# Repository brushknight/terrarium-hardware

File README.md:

## I have to pull this project back from public because I am considering manufacturing of the controller and for a period of time we will not publish schematics. Once I release controller I will consider publishing schematics again.

---

# Terrarium controller (esp32 based)
[more details here](./controller/README.md)

This terrarium controller is capable of controlling set temperature, heat, and UVB lamps taking into account the time of the day.

## Features
- ESP32 WROOM 32 as a main brain of the system
- EEPROM i2c DIP-8 socket for user configuration storage
- 6 x 5v i2c & 1wire sensors
- 4 x 5v SSR to drive up to 3 x 220v2A loads
  - Protected by SMD fuse with max current limited to 1.5A/220V
- 2 x 5v 3/4pin PWM fan support
- i2c Display to show crusial information
- i2c RTC DS3231M + battery to keep time between power outages
- i2c multiplexer TCA9548APWR
- i2c IO expander PCF8574
- i2c extensions port
- cp2102 USB to UART
  - It is bidirectional now
  - Includes ESD protection
- USB-C for power and flashing
- 0805 components size

---

# Terrarium dimmer (esp32 based)
[more details here](./dimmer/README.md)

This terrarium dimmer is capable of controlling brightness of the incandescent lamps taking into account the time of the day.

## Features
- ESP32 WROOM 32 as a main brain of the system
- 2 pwm dimmer modules
- i2c extension port (used for connecting to the main controller)
- cp2102 USB to UART
- USB-C for power and flashing

---

# Terrarium light dome (esp32 based)
[more details here](./light_dome/README.md)

This terrarium dome is capable to provide some light with simple ws2812b LEDs. The meain goal right now is to create circadian lights for the reptiles so it is not on/off of the UVB bulb.

In the next iterations I am planning to do a research about UV LEDs and other more reptiles oriented LEDs.

## Features
- ESP32 WROOM 32 as a main brain of the system
- 20 x 3 (60 in total) ws2812b LEDs
- i2c extension port (used for connecting to the main controller)
- cp2102 USB to UART
- USB-C for power and flashing

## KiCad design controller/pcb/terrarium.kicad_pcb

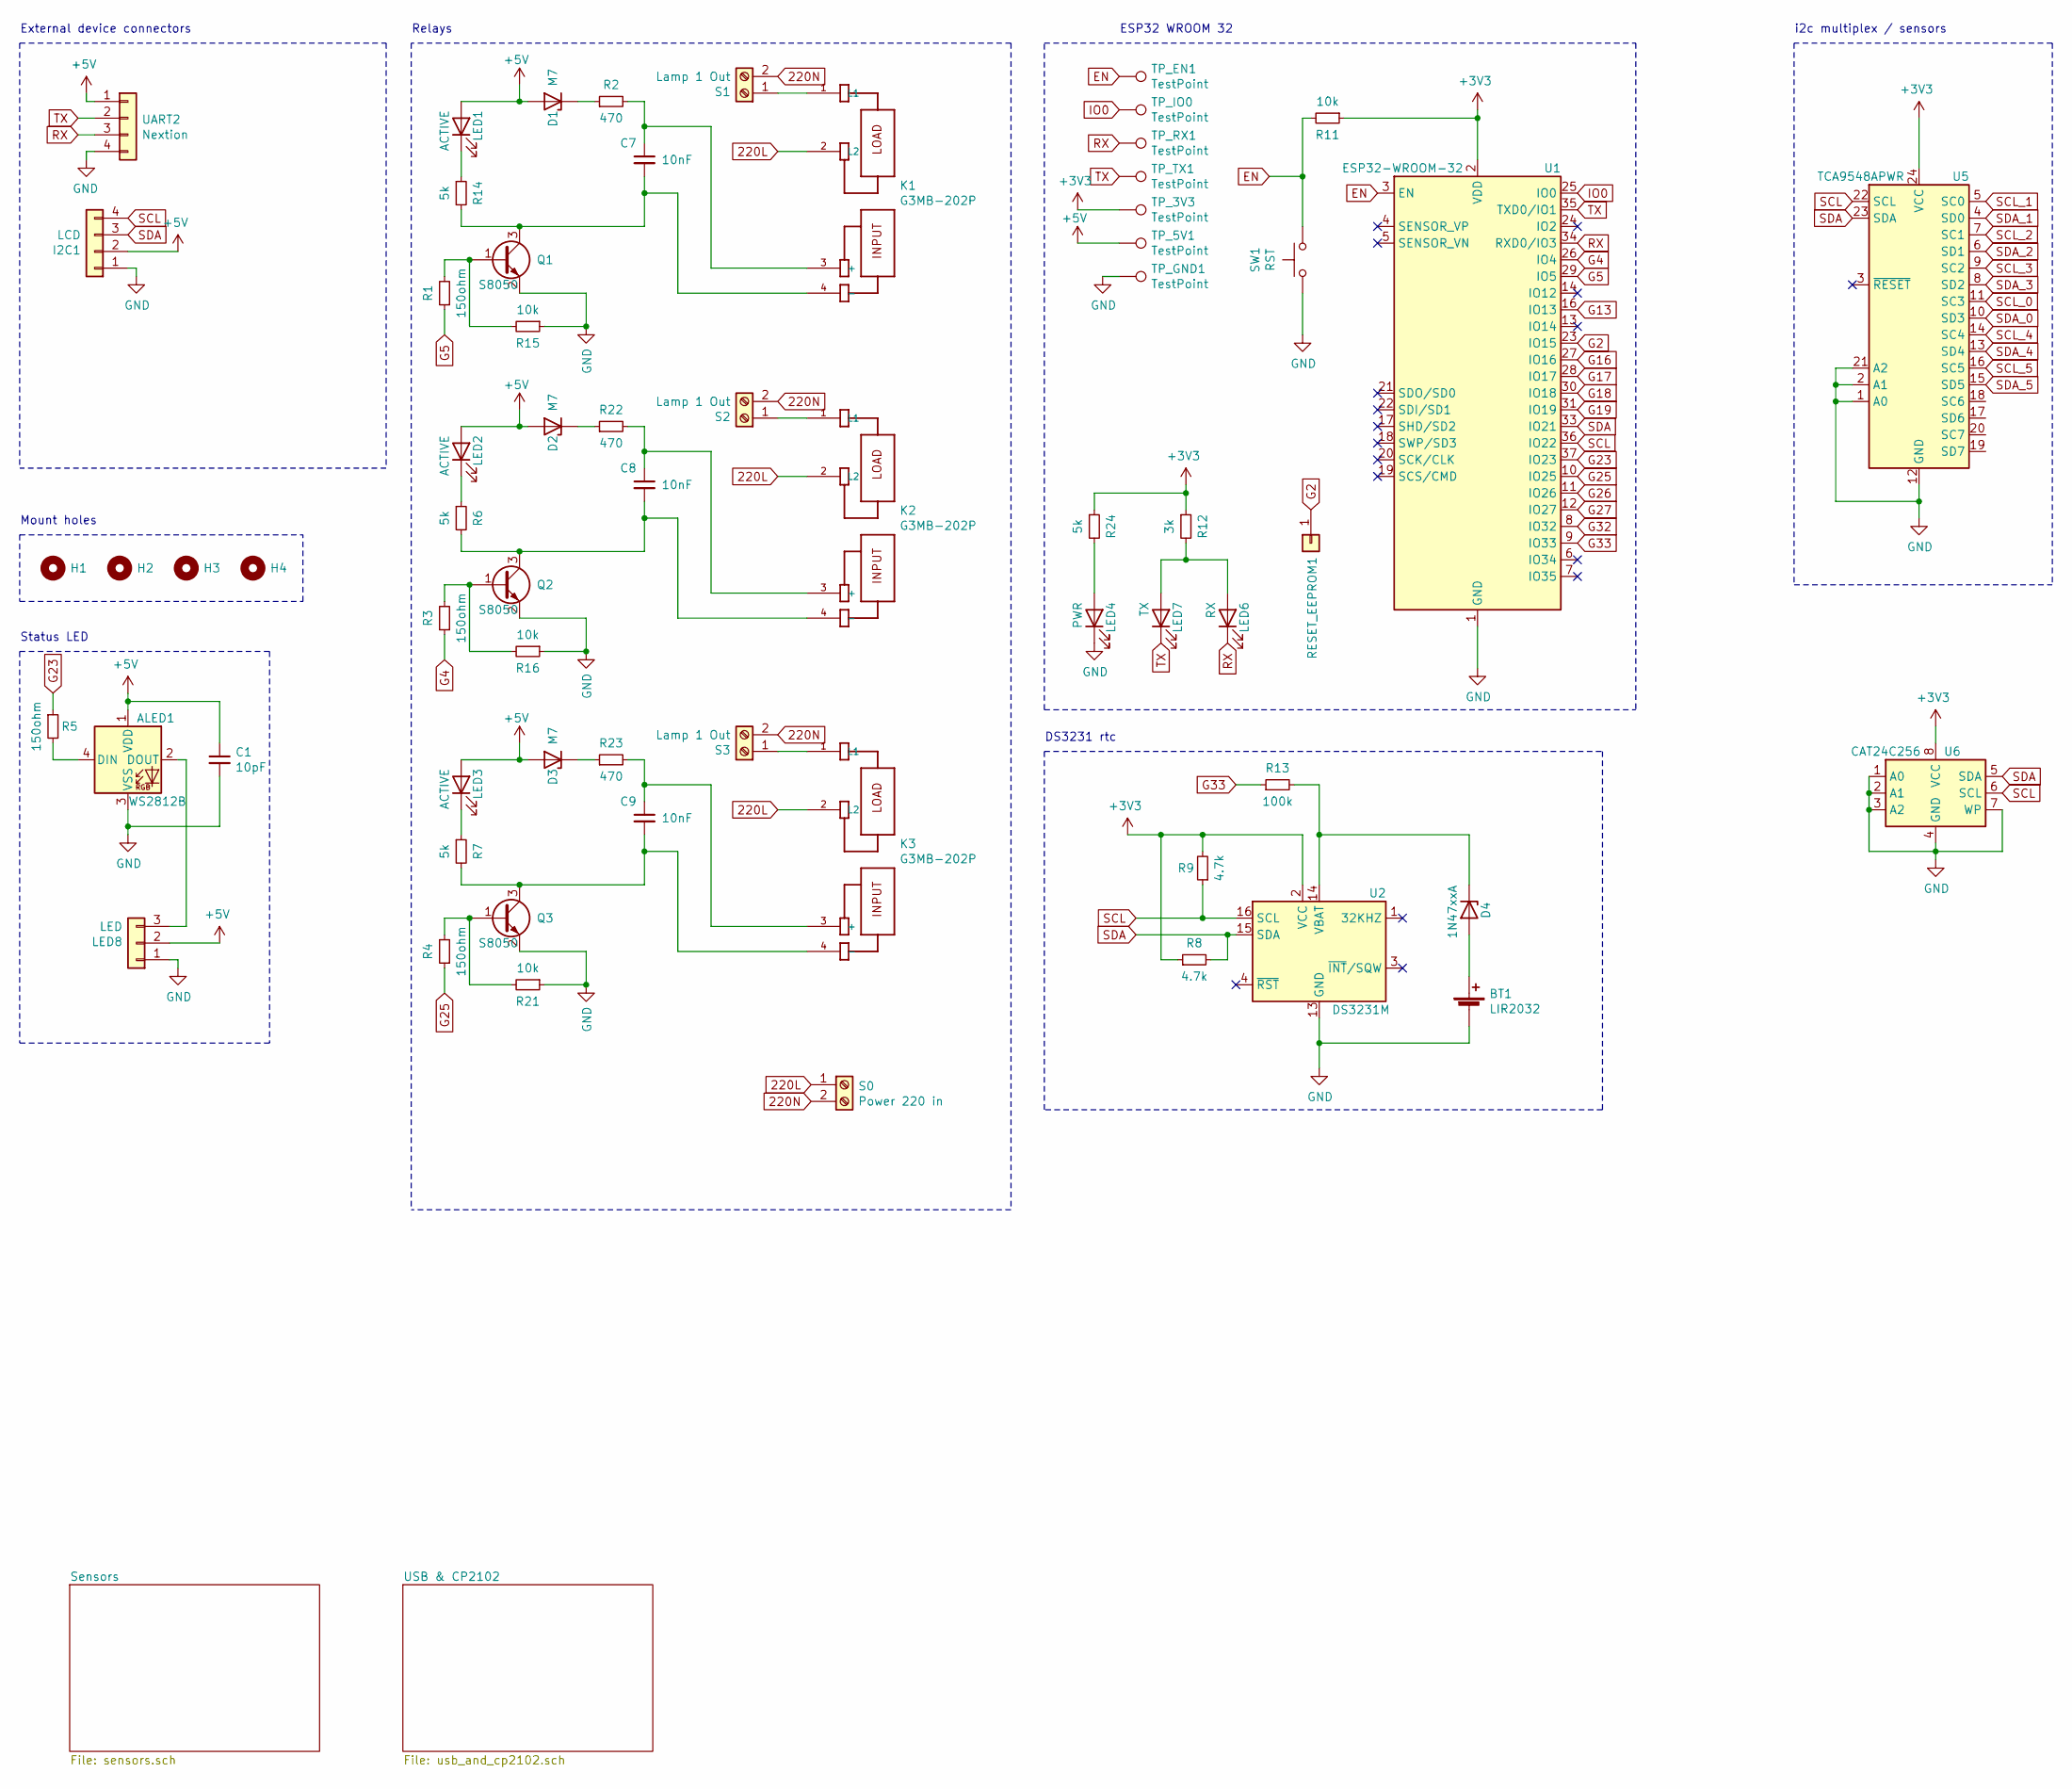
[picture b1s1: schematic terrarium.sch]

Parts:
ALED1: WS2812B; LED_WS2812B_PLCC4_5.0x5.0mm_P3.2mm
BT1: LIR2032; CR2032_vertical
C1: 10pF; C_1206_3216Metric
C7, C8, C9: 10nF; C_1206_3216Metric
D1, D2, D3: M7; D_2010_5025Metric
D4: 1N47xxA; D_2010_5025Metric
H1, H2, H3, H4: MountingHole; MountingHole_3.2mm_M3_Pad_Via
I2C1: LCD; JST_XH_B4B-XH-AM_1x04_P2.50mm_Vertical
K1, K2, K3: G3MB-202P; RELAY_G3MB-202P
LED1, LED2, LED3: ACTIVE; LED_1206_3216Metric
LED4: PWR; LED_1206_3216Metric
LED6: RX; LED_1206_3216Metric
LED7: TX; LED_1206_3216Metric
LED8: LED; JST_XH_B3B-XH-A_1x03_P2.50mm_Vertical
Q1, Q2, Q3: S8050; SOT-23
R1, R3, R4, R5: 150ohm; R_1206_3216Metric
R2, R22, R23: 470; R_1206_3216Metric
R6, R7, R14, R24: 5k; R_1206_3216Metric
R8, R9: 4.7k; R_1206_3216Metric
R11, R15, R16, R21: 10k; R_1206_3216Metric
R12: 3k; R_1206_3216Metric
R13: 100k; R_1206_3216Metric
RESET_EEPROM1: data; PinHeader_1x01_P2.54mm_Vertical
S0: Power 220 in; TerminalBlock_bornier-2_P5.08mm
S1, S2, S3: Lamp 1 Out; TerminalBlock_bornier-2_P5.08mm
SW1: RST; SW_Tactile_SPST_Angled_PTS645Vx39-2LFS
TP_3V3, TP_5V1: TestPoint; TestPoint_Pad_1.5x1.5mm
TP_EN1: TestPoint; TestPoint_Pad_1.5x1.5mm
TP_GND1: TestPoint; TestPoint_Pad_1.5x1.5mm
TP_IO0: TestPoint; TestPoint_Pad_1.5x1.5mm
TP_RX1: TestPoint; TestPoint_Pad_1.5x1.5mm
TP_TX1: TestPoint; TestPoint_Pad_1.5x1.5mm
U1: ESP32-WROOM-32
U2: DS3231M; SOIC-16W_7.5x10.3mm_P1.27mm
U5: TCA9548APWR; TSSOP-24_4.4x7.8mm_P0.65mm
U6: CAT24C256; DIP-8_W7.62mm_Socket
UART2: Nextion; JST_XH_B4B-XH-AM_1x04_P2.50mm_Vertical

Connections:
220L: K1.2 (L2), K2.2 (L2), K3.2 (L2), S0.1
220N: S0.2, S1.2, S2.2, S3.2
+3V3: R8.1, R9.2, R11.1, R12.1, R24.1, TP_3V3.1, U1.2 (VDD), U2.2 (VCC), U5.24 (VCC), U6.8 (VCC); also elsewhere on the board
+5V: ALED1.1 (VDD), C1.1, D1.2 (A), D2.2 (A), D3.2 (A), I2C1.2, LED1.2 (A), LED2.2 (A), LED3.2 (A), LED8.2, TP_5V1.1, UART2.1; also elsewhere on the board
EN: R11.2, SW1.2, TP_EN1.1, U1.3 (EN); also elsewhere on the board
G2: RESET_EEPROM1.1, U1.23 (IO15)
G4: R3.1, U1.26 (IO4)
G5: R1.1, U1.29 (IO5)
G13: U1.16 (IO13)
G16: U1.27 (IO16); also elsewhere on the board
G17: U1.28 (IO17); also elsewhere on the board
G18: U1.30 (IO18); also elsewhere on the board
G19: U1.31 (IO19); also elsewhere on the board
G23: R5.1, U1.37 (IO23)
G25: R4.1, U1.10 (IO25)
G26: U1.11 (IO26); also elsewhere on the board
G27: U1.12 (IO27); also elsewhere on the board
G32: U1.8 (IO32); also elsewhere on the board
G33: R13.1, U1.9 (IO33)
GND: ALED1.3 (VSS), BT1.2 (-), C1.2, I2C1.1, LED4.1 (K), LED8.1, Q1.2 (E), Q2.2 (E), Q3.2 (E), R15.1, R16.1, R21.1, SW1.1, TP_GND1.1, U1.1 (GND), U1.15 (GND), U1.38 (GND), U1.39 (GND), U2.5 (GND), U2.6 (GND), U2.7 (GND), U2.8 (GND), U2.9 (GND), U2.10 (GND), U2.11 (GND), U2.12 (GND), U2.13 (GND), U5.1 (A0), U5.2 (A1), U5.12 (GND), U5.21 (A2), U6.1 (A0), U6.2 (A1), U6.3 (A2), U6.4 (GND), U6.7 (WP), UART2.4; also elsewhere on the board
IO0: TP_IO0.1, U1.25 (IO0); also elsewhere on the board
unnamed: ALED1.2 (DOUT), LED8.3
unnamed: ALED1.4 (DIN), R5.2
unnamed: BT1.1 (+), D4.2 (A)
unnamed: C7.1, K1.3 (+), R2.2
unnamed: C7.2, K1.4 (-), Q1.3 (C), R14.2
unnamed: C8.1, K2.3 (+), R22.2
unnamed: C8.2, K2.4 (-), Q2.3 (C), R6.2
unnamed: C9.1, K3.3 (+), R23.2
unnamed: C9.2, K3.4 (-), Q3.3 (C), R7.2
unnamed: D1.1 (K), R2.1
unnamed: D2.1 (K), R22.1
unnamed: D3.1 (K), R23.1
unnamed: D4.1 (K), R13.2, U2.14 (VBAT)
unnamed: K1.1 (L1), S1.1
unnamed: K2.1 (L1), S2.1
unnamed: K3.1 (L1), S3.1
unnamed: LED1.1 (K), R14.1
unnamed: LED2.1 (K), R6.1
unnamed: LED3.1 (K), R7.1
unnamed: LED4.2 (A), R24.2
unnamed: LED6.2 (A), LED7.2 (A), R12.2
unnamed: Q1.1 (B), R1.2, R15.2
unnamed: Q2.1 (B), R3.2, R16.2
unnamed: Q3.1 (B), R4.2, R21.2
unnamed 58: U5.3 (~RESET); also elsewhere on the board
RX: LED6.1 (K), TP_RX1.1, U1.34 (RXD0/IO3), UART2.3; also elsewhere on the board
SCL: I2C1.4, R9.1, U1.36 (IO22), U2.16 (SCL), U5.22 (SCL), U6.6 (SCL); also elsewhere on the board
SCL_0: U5.11 (SC3); also elsewhere on the board
SCL_1: U5.5 (SC0); also elsewhere on the board
SCL_2: U5.7 (SC1); also elsewhere on the board
SCL_3: U5.9 (SC2); also elsewhere on the board
SCL_4: U5.14 (SC4); also elsewhere on the board
SCL_5: U5.16 (SC5); also elsewhere on the board
SDA: I2C1.3, R8.2, U1.33 (IO21), U2.15 (SDA), U5.23 (SDA), U6.5 (SDA); also elsewhere on the board
SDA_0: U5.10 (SD3); also elsewhere on the board
SDA_1: U5.4 (SD0); also elsewhere on the board
SDA_2: U5.6 (SD1); also elsewhere on the board
SDA_3: U5.8 (SD2); also elsewhere on the board
SDA_4: U5.13 (SD4); also elsewhere on the board
SDA_5: U5.15 (SD5); also elsewhere on the board
TX: LED7.1 (K), TP_TX1.1, U1.35 (TXD0/IO1), UART2.2; also elsewhere on the board

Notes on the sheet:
External device connectors
Relays
Status LED
ESP32 WROOM 32
DS3231 rtc
Mount holes
i2c multiplex / sensors

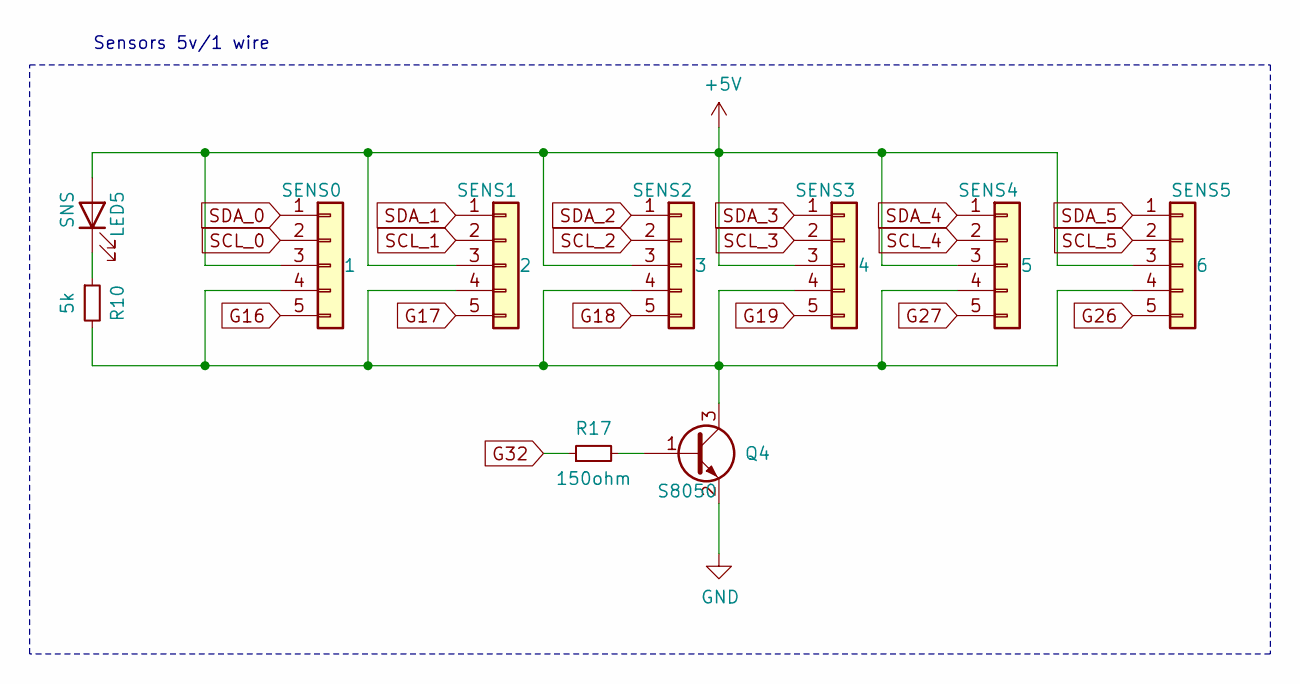
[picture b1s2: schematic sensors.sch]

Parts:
LED5: SNS; LED_1206_3216Metric
Q4: S8050; SOT-23
R10: 5k; R_1206_3216Metric
R17: 150ohm; R_1206_3216Metric
SENS0: 1; JST_XH_B5B-XH-A_1x05_P2.50mm_Vertical
SENS1: 2; JST_XH_B5B-XH-A_1x05_P2.50mm_Vertical
SENS2: 3; JST_XH_B5B-XH-A_1x05_P2.50mm_Vertical
SENS3: 4; JST_XH_B5B-XH-AM_1x05_P2.50mm_Vertical
SENS4: 5; JST_XH_B6B-XH-AM_1x06_P2.50mm_Vertical
SENS5: 6; JST_XH_B5B-XH-A_1x05_P2.50mm_Vertical

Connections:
+5V: LED5.2 (A), SENS0.3, SENS1.3, SENS2.3, SENS3.3, SENS4.3, SENS5.3; also elsewhere on the board
G16: SENS0.5; also elsewhere on the board
G17: SENS1.5; also elsewhere on the board
G18: SENS2.5; also elsewhere on the board
G19: SENS3.5; also elsewhere on the board
G26: SENS5.5; also elsewhere on the board
G27: SENS4.5; also elsewhere on the board
G32: R17.1; also elsewhere on the board
GND: Q4.2 (E); also elsewhere on the board
unnamed: LED5.1 (K), R10.1
unnamed: Q4.1 (B), R17.2
unnamed: Q4.3 (C), R10.2, SENS0.4, SENS1.4, SENS2.4, SENS3.4, SENS4.4, SENS5.4
SCL_0: SENS0.2; also elsewhere on the board
SCL_1: SENS1.2; also elsewhere on the board
SCL_2: SENS2.2; also elsewhere on the board
SCL_3: SENS3.2; also elsewhere on the board
SCL_4: SENS4.2; also elsewhere on the board
SCL_5: SENS5.2; also elsewhere on the board
SDA_0: SENS0.1; also elsewhere on the board
SDA_1: SENS1.1; also elsewhere on the board
SDA_2: SENS2.1; also elsewhere on the board
SDA_3: SENS3.1; also elsewhere on the board
SDA_4: SENS4.1; also elsewhere on the board
SDA_5: SENS5.1; also elsewhere on the board

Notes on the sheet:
Sensors 5v/1 wire

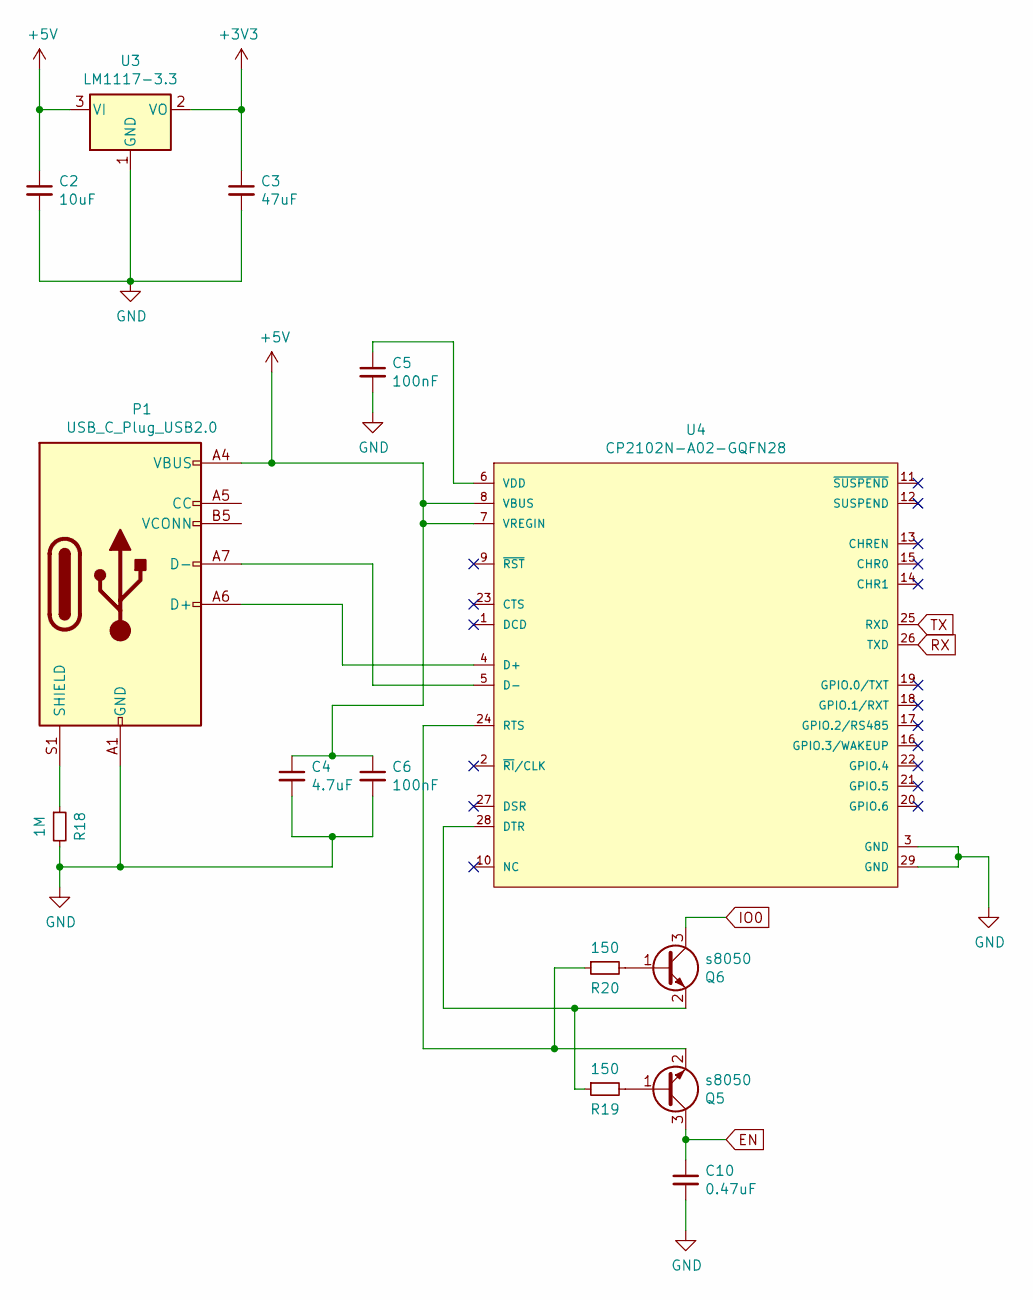
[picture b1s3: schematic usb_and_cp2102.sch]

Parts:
C2: 10uF; C_1206_3216Metric
C3: 47uF; C_1206_3216Metric
C4: 4.7uF; C_1206_3216Metric
C5, C6: 100nF; C_1206_3216Metric
C10: 0.47uF; C_1206_3216Metric
P1: USB_C_Plug_USB2.0; USB_C_Receptacle_Palconn_UTC16-G
Q5, Q6: s8050; SOT-23
R18: 1M; R_1206_3216Metric
R19, R20: 150; R_1206_3216Metric
U3: LM1117-3.3; SOT-223-3_TabPin2
U4: CP2102N-A02-GQFN28; Silicon_Labs-CP2102N-A02-GQFN28-IPC_A; mouser part number 634-CP2102NA02GQFN28; digikey description IC USB TO UART BRIDGE QFN28

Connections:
+3V3: C3.1, U3.2 (VO); also elsewhere on the board
+5V: C2.1, C4.1, C6.1, P1.A4 (VBUS), P1.A9 (VBUS), P1.B4 (VBUS), P1.B9 (VBUS), U3.3 (VI), U4.7 (VREGIN), U4.8 (VBUS); also elsewhere on the board
EN: C10.1, Q5.3 (C); also elsewhere on the board
GND: C2.2, C3.2, C4.2, C5.2, C6.2, C10.2, P1.A1 (GND), P1.A12 (GND), P1.B1 (GND), P1.B12 (GND), R18.2, U3.1 (GND), U4.3 (GND), U4.29 (GND); also elsewhere on the board
IO0: Q6.3 (C); also elsewhere on the board
unnamed: C5.1, U4.6 (VDD)
unnamed: P1.A6 (D+), U4.4 (D+)
unnamed: P1.A7 (D-), U4.5 (D-)
unnamed: P1.S1 (SHIELD), R18.1
unnamed: Q5.1 (B), R19.2
unnamed: Q5.2 (E), R20.1, U4.24 (RTS)
unnamed: Q6.1 (B), R20.2
unnamed: Q6.2 (E), R19.1, U4.28 (DTR)
RX: U4.26 (TXD); also elsewhere on the board
TX: U4.25 (RXD); also elsewhere on the board

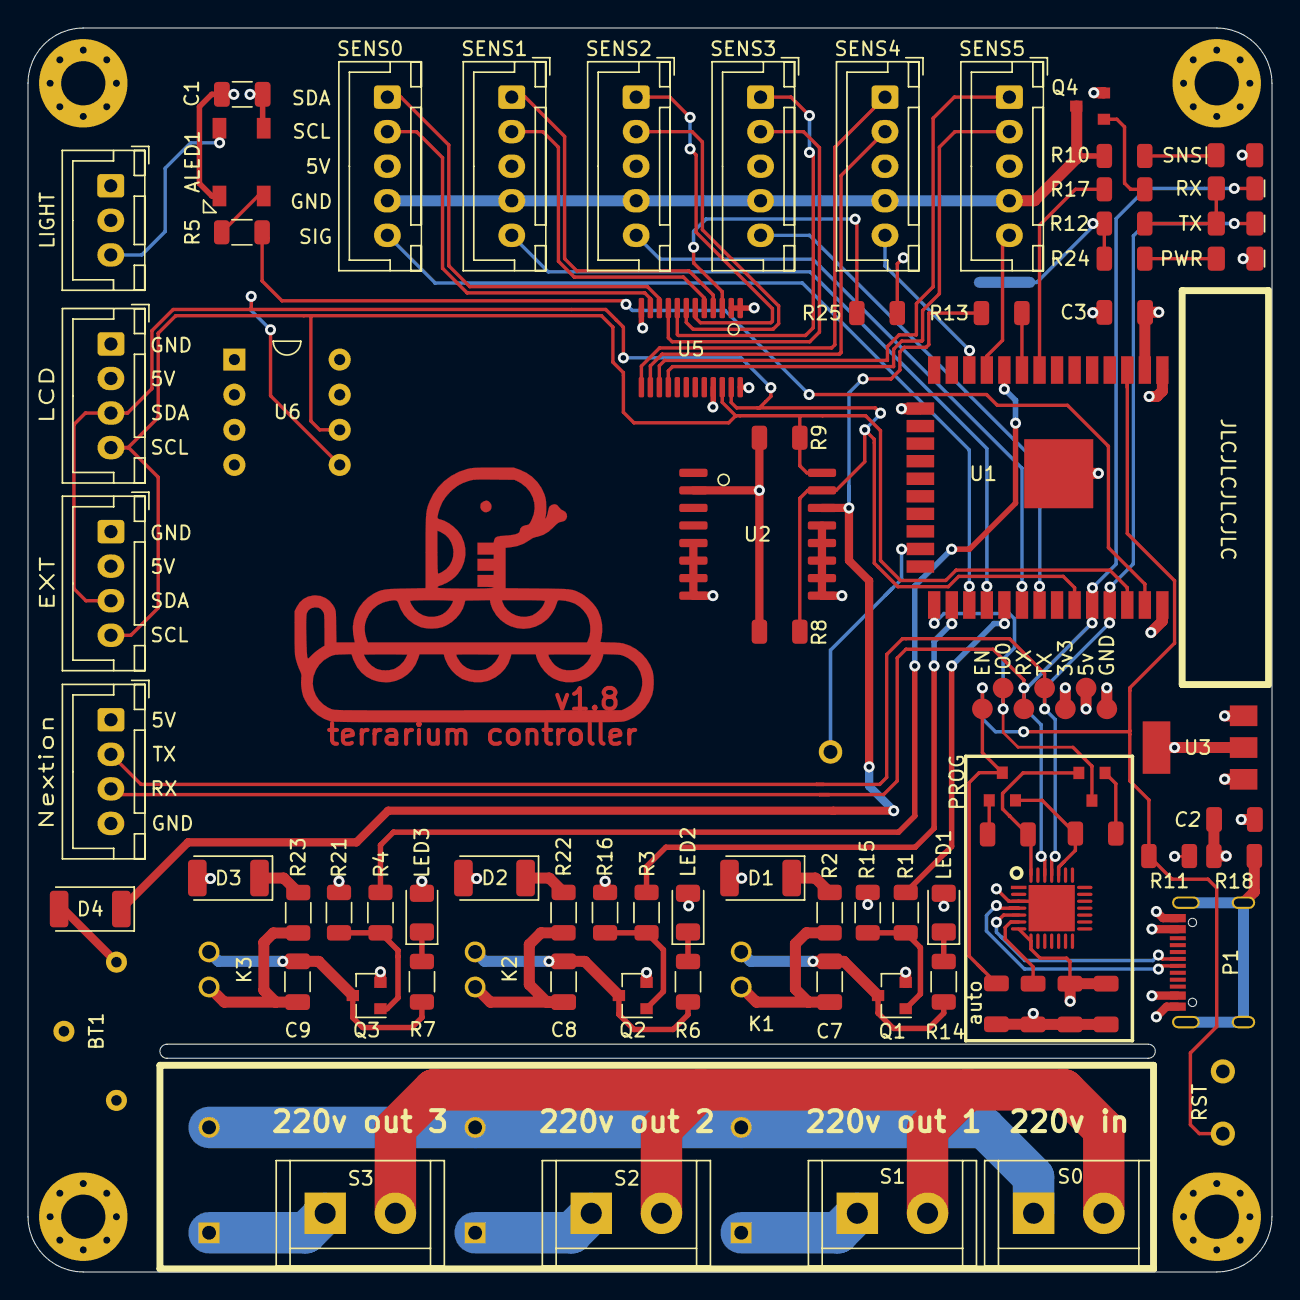
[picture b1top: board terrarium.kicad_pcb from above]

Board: 4 copper layers, 90.0 x 90.0 mm, 91 parts (0 on the bottom side), 72 nets.

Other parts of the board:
I2C2: EXT; JST_XH_B4B-XH-A_1x04_P2.50mm_Vertical
R25: 10k; R_1206_3216Metric

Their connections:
+3V3: R25.1; also elsewhere on the board
+5V: I2C2.2; also elsewhere on the board
GND: I2C2.1; also elsewhere on the board
unnamed 58: R25.2; also elsewhere on the board
SCL: I2C2.4; also elsewhere on the board
SDA: I2C2.3; also elsewhere on the board

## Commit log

2021-12-25 pcb: refactor
2021-12-27 minor updates, bjt to sot-23
2021-12-31 rtc charge, refactoring
2022-01-01 update jst footprints, added missing 3d models
2022-01-02 refactoring
2022-01-05 minor changes
2022-01-06 diode for battery
2022-01-08 fix bugs in UART
2022-01-08 add transistor for sensors
2022-01-09 move status led from relay circuit
2022-01-10 pcb v1.4 release
2022-01-10 fix snake logo
2022-02-11 feat: add 5 pin sensor connectors
2022-02-12 wip qnfp28
2022-03-10 rearrange components
2022-03-10 fix bugs, update button footprint
2022-03-11 update ssr circuits
2022-03-25 release
2022-06-20 pcb v1.7 done
2022-06-20 Controller pcb/v1.7 (#5)
    * move components around
    * pcb v1.7 done
2022-07-04 change programming header to test pads
2022-07-04 rearrage some components
2022-07-18 improved silk screen, tracing
